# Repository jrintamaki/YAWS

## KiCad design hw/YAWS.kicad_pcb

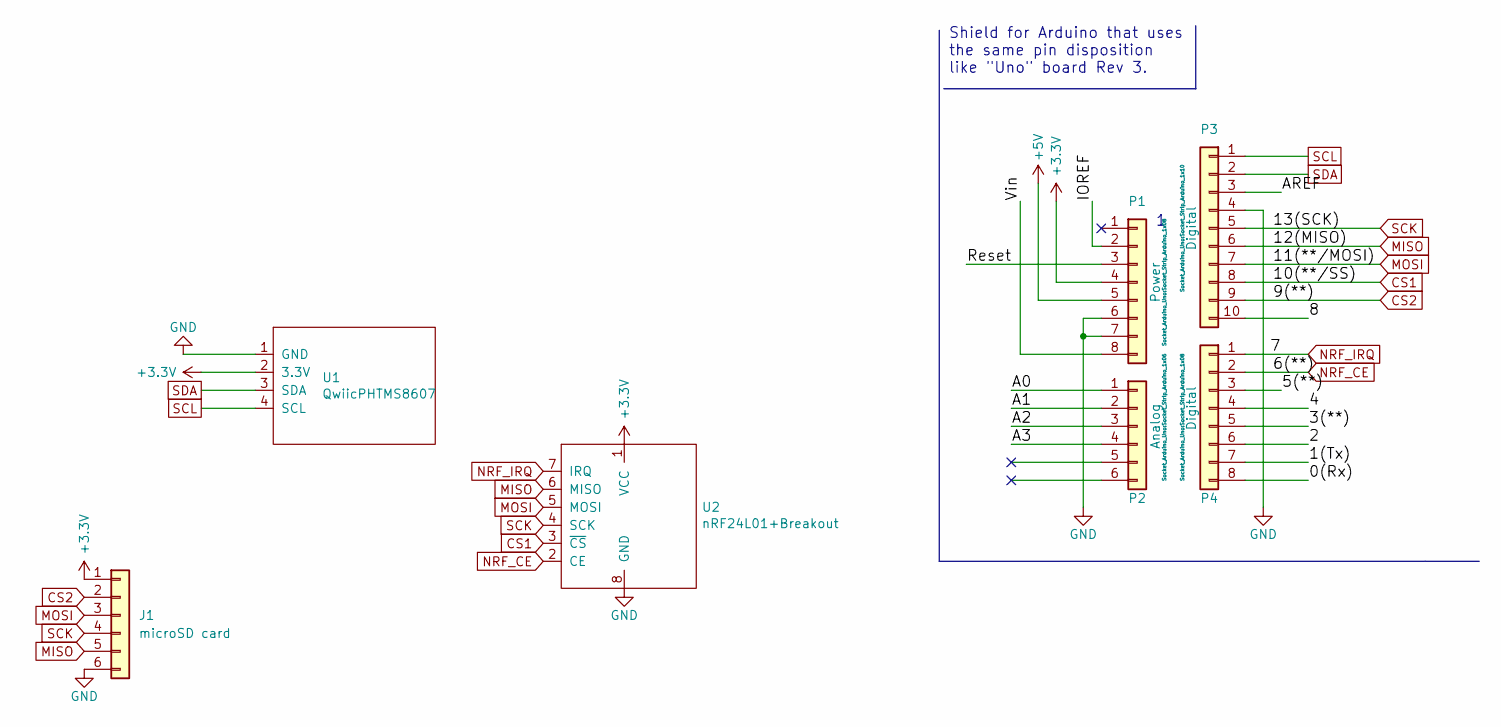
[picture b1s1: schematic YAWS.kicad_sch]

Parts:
J1: microSD card; PinHeader_1x06_P2.54mm_Vertical
P1: Power; Socket_Strip_Arduino_1x08
P2: Analog; Socket_Strip_Arduino_1x06
P3: Digital; Socket_Strip_Arduino_1x10
P4: Digital; Socket_Strip_Arduino_1x08
U1: QwiicPHTMS8607; PinHeader_1x04_P2.54mm_Vertical
U2: nRF24L01+Breakout; PinHeader_1x08_P2.54mm_Vertical

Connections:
+3V3: J1.1, P1.4, U1.2 (3.3V), U2.1 (VCC)
+5V: P1.5
/0(Rx): P4.8
/1(Tx): P4.7
/2: P4.6
/3(**): P4.5
/4: P4.4
/5(**): P4.3
/8: P3.10
/A0: P2.1
/A1: P2.2
/A2: P2.3
/A3: P2.4
/AREF: P3.3
/IOREF: P1.2
/Reset: P1.3
/Vin: P1.8
CS1: P3.8, U2.3 (~CS)
CS2: J1.2, P3.9
GND: J1.6, P1.6, P1.7, P3.4, U1.1 (GND), U2.8 (GND)
MISO: J1.5, P3.6, U2.6 (MISO)
MOSI: J1.3, P3.7, U2.5 (MOSI)
NRF_CE: P4.2, U2.2 (CE)
NRF_IRQ: P4.1, U2.7 (IRQ)
SCK: J1.4, P3.5, U2.4 (SCK)
SCL: P3.1, U1.4 (SCL)
SDA: P3.2, U1.3 (SDA)

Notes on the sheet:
Shield for Arduino that uses the same pin disposition like "Uno" board Rev 3.

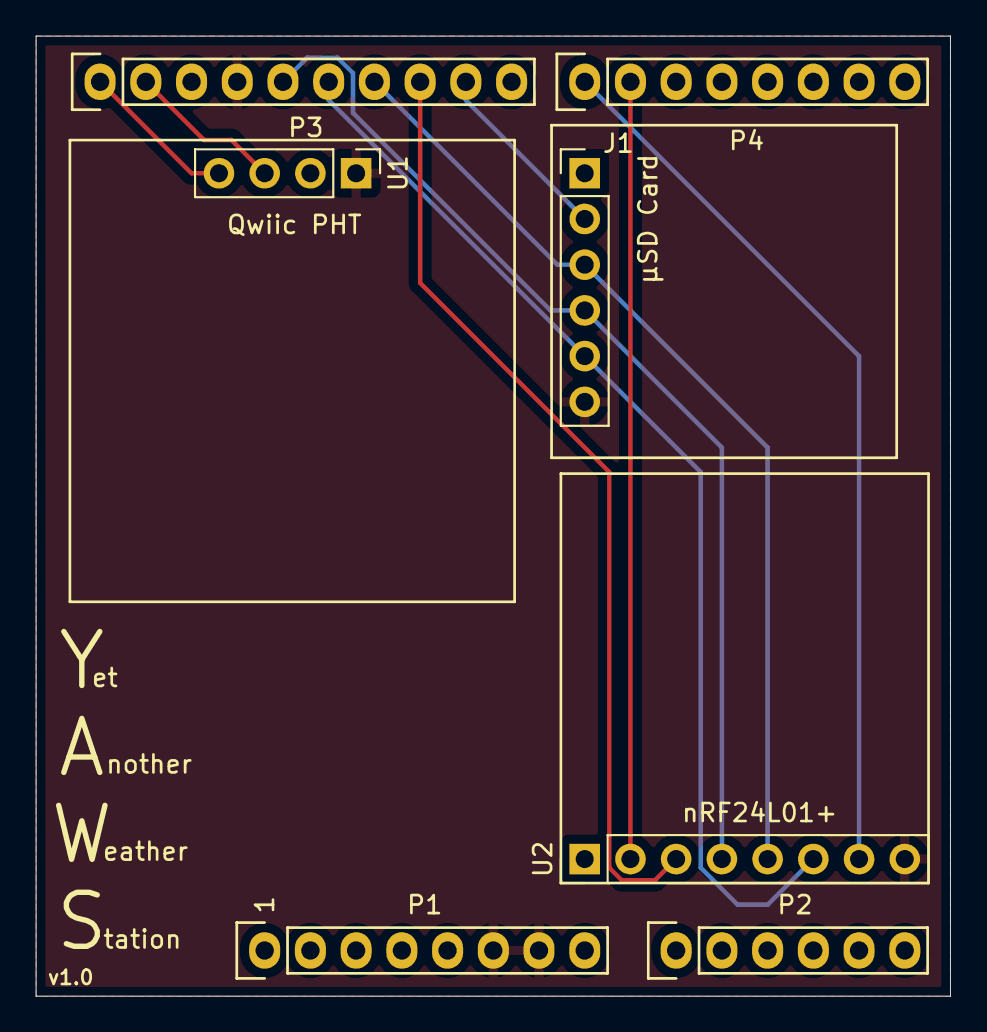
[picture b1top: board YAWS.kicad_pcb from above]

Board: 2 copper layers, 50.8 x 53.3 mm, 7 parts (0 on the bottom side), 11 nets.

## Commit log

2022-03-09 Initial commit for YAWS
2022-03-09 Add intial BLE functions to YAWS
2022-03-15 Clean repo
2022-03-23 Add SD card library and initial functionality
2022-04-23 Add working SD communication and fix PHT usage
2022-05-11 Add BLE driver
2022-05-11 Clean YAWS code and drivers
2022-05-12 Change the periodic waiting time to happen when broadcasting data
    Broadcasted data is also changed between advertisement runs
2022-05-12 Remove unecessary nRF24L01P lib
2022-05-15 Add hw kicad stuff
